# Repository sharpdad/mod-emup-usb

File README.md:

# MOD-EMUP over USB

Bring a 1990s universal device programmer back to life on a modern computer.

The **MOD-EMUP** (sold by JDR Microdevices; the same machine as the Hi-Lo
**ALL-03**, the Tribal TUP-400 and the Expro-60) programs parts that modern
programmers won't touch: bipolar PROMs (82S123, 82S129, 74S287, ...), old
PALs, GALs, PEELs and EPROMs. Arcade and vintage-computer people still need
those. But the box only talks to an 8-bit ISA card and DOS software.

This project replaces the ISA card with a small USB adapter and the DOS
software with a desktop app.

| | |
|---|---|
| **Status** | Designed, simulated and unit-tested. **Not yet tried on a real box.** |
| **Why it's posted** | The original author ran out of time. Everything needed to finish it is here; the missing piece is someone with a box, a meter and an afternoon. |

## What's here

| Folder | What | State |
|---|---|---|
| [`hardware/`](hardware/) | USB adapter PCB (KiCad 8): Arduino Nano, 74HCT245 / 74HCT244 bus buffers, DB25 to the box, and **one 12 V supply** for everything: +12 V passed through, +5 V 2 A from a RECOM R-78B switching module, -12 V from an isolated TRACO TMR 1-1211. All through-hole. Gerbers and BOM in `hardware/fab/`. Or build it on a breadboard with an old PC power supply: [`docs/BREADBOARD.md`](docs/BREADBOARD.md). | Routed, DRC clean. Not fabricated. |
| [`firmware/emup_usb/`](firmware/emup_usb/) | Arduino sketch: runs batches of register writes, reads and timed delays sent over USB serial (1 Mbaud), so programming pulses are timed on the adapter, not across USB. | Compiles in principle; untested. |
| [`app/`](app/) | **EMUP Studio**, a Tauri app (Rust + HTML) for macOS, Windows and Linux: chip search, a drawing of where the chip goes in the socket, drag-and-drop .bin / .hex / .jed, hex view, checksums, Read / Blank / Program / Verify. | Runs. 2716 read/program and 2732 read are implemented at register level against a model of the box; other chips use a placeholder. |
| [`dosbox-x/`](dosbox-x/) | A DOSBox-X patch that logs every port access the original DOS programs make, to learn each chip family's algorithm (voltages, pins, timings) without disassembling them. | Works; findings in its README. |
| [`docs/`](docs/) | [Register map and cable pinout](docs/NOTES.md), notes. | |
| [`tools/kicad/`](tools/kicad/) | The scripts that generate the KiCad schematic and routed PCB from `hardware/emup_adapter.py`. | Works. |

## How the box works

The ISA card is just a buffered bus extender: an 8-bit data bus and three
strobes go down a DB25 cable. Everything else is in the box. Software
writes a register number to the card's **ID port**, then reads or writes
that register through the **data port**:

| Register | Does |
|---|---|
| E0-E4 | TTL I/O for socket pins 1-40 (open collector: write 1 before reading or applying a supply) |
| E5 / E6 / E7 | VOP (0.1 V steps) / VHH (0.06 V) / VCC (0.04 V) DACs |
| E8-EC, F0-F4 | switch VOP / VHH onto socket pins |
| ED-EE | switch VCC onto a fixed set of pins |
| EF | ground selection (pin 20 or pins 11 / 30), clocks |
| F7 | bit 3: GOOD lamp |

Full map and the DB25 pinout: [docs/NOTES.md](docs/NOTES.md). Chips sit at
the bottom of the 40-pin socket; chip pin *k* lands on socket pin
*k* + 20 - pins/2, so a 2716's ground lands on socket pin 20 and its VCC on
pin 32, both of which the box can switch.

## Building the adapter

1. Order the board from `hardware/fab/emup_adapter_gerbers.zip` (any 2-layer
   fab) and the parts in `hardware/fab/bom.csv`.
2. **Before plugging into a box:** check the DB25 pinout in
   [docs/NOTES.md](docs/NOTES.md) against your box with a meter. It comes from
   Tom Trebisky's notes on his card; boxes and cables may differ.
3. Power the board alone from a 12 V, 2 A supply (2.1 mm, centre positive)
   and check +5 V, +12 V and -12 V on the DB25 pins.
4. Flash `firmware/emup_usb/emup_usb.ino` to the Nano (Arduino IDE).
5. Connect the box, run the app, pick the adapter's serial port.

The box's real current draw is unknown. The +5 V module gives 2 A and the
-12 V module about 80 mA; measure the box and change the modules if needed.

## Building the app

```sh
cd app/src-tauri
cargo install tauri-cli --version "^2"
cargo tauri dev        # run
cargo tauri build      # make an installable app
cargo test             # the box model: read and program a virtual 2716
```

Needs Rust ([rustup.rs](https://rustup.rs)). Windows also needs WebView2,
which Windows 10 and 11 include.

## What's left to do (good first issues)

* **Try it on a real box.** Measure current draw, confirm the pinout, read a
  known 2716 and compare it with a dump made elsewhere.
* **The identification check.** Every DOS program first checks the box: it
  writes 00, 01, 00, 02 and then pulses to register E7 and reads the low
  nibble of register **F8**, which the ALL-03 documentation doesn't mention.
  The app doesn't need it, but it shows there's logic in the box we don't
  fully understand. See [dosbox-x/README.md](dosbox-x/README.md).
* **More chip algorithms** in `app/src-tauri/src/emup.rs`: 2732 / 27xx
  programming, bipolar PROMs (fuse blowing: VOP pulses on the outputs),
  PAL/GAL programming from JEDEC fuse maps. Record the DOS programs with the
  DOSBox-X patch to see exactly what they do.
* **Release builds** of EMUP Studio for macOS / Windows / Linux (GitHub
  Actions can build all three).

## Credits and sources

* Tom Trebisky's pages on the MOD-EMUP and ALL-03 (cable, card, protocol):
  http://cholla.mmto.org/proms/emup/
* The ALL-03 register description (`all03info.txt`, by the manufacturer,
  with a note by Fabio Sturman) and the ALL-03 manual, findable in vintage
  programmer archives.

The original DOS software, sample images and third-party documents are not
included; find them through the links above.

## Licence

Code (app, firmware, tools, patch): MIT, see [LICENSE](LICENSE); the DOSBox-X
patch is GPL-2.0 like DOSBox-X. Hardware design: CERN-OHL-P-2.0.

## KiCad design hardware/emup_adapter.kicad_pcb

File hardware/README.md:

# The USB adapter PCB

`emup_adapter.py` describes the board (parts, nets, placement);
`./build.sh` turns it into the KiCad schematic (`emup_adapter.kicad_sch`,
`.pdf`), a routed PCB (`emup_adapter.kicad_pcb`), DRC / ERC reports and fab
files (`fab/`: Gerber + drill zip, BOM). The KiCad files open and edit
normally in KiCad 8; if you edit the board by hand, don't re-run build.sh.

* Power: one 12 V DC supply (2.1 mm barrel, centre positive, 2 A) through
  a 1N5822. +12 V goes to the box as is; +5 V (2 A) comes from a RECOM
  R-78B5.0-2.0 (7805-footprint switching module); -12 V from a TRACO TMR
  1-1211 isolated module with its +output tied to ground (about 80 mA). The
  power nets are 1 mm tracks (`netclasses.json`).
* Logic: an Arduino Nano (5 V, on USB) drives D0-D7 through a 74HCT245
  (direction from D10) and the strobes /WRID, /WRDAT, /RDDAT and /RESET
  through a 74HCT244 (from A0-A3). 10k pull-ups hold the strobes idle while
  the Nano boots. The buffers run from the board's +5 V.
* DB25 female, wired as the original SAC-201 card (pinout in
  ../docs/NOTES.md). Check it against your box first.

Untested. Things to check on the first board: the box's current on each
rail, the -12 V module's load, the DB25 pinout, and the strobe timing (the
firmware uses ~1 us strobes, like the ISA bus).

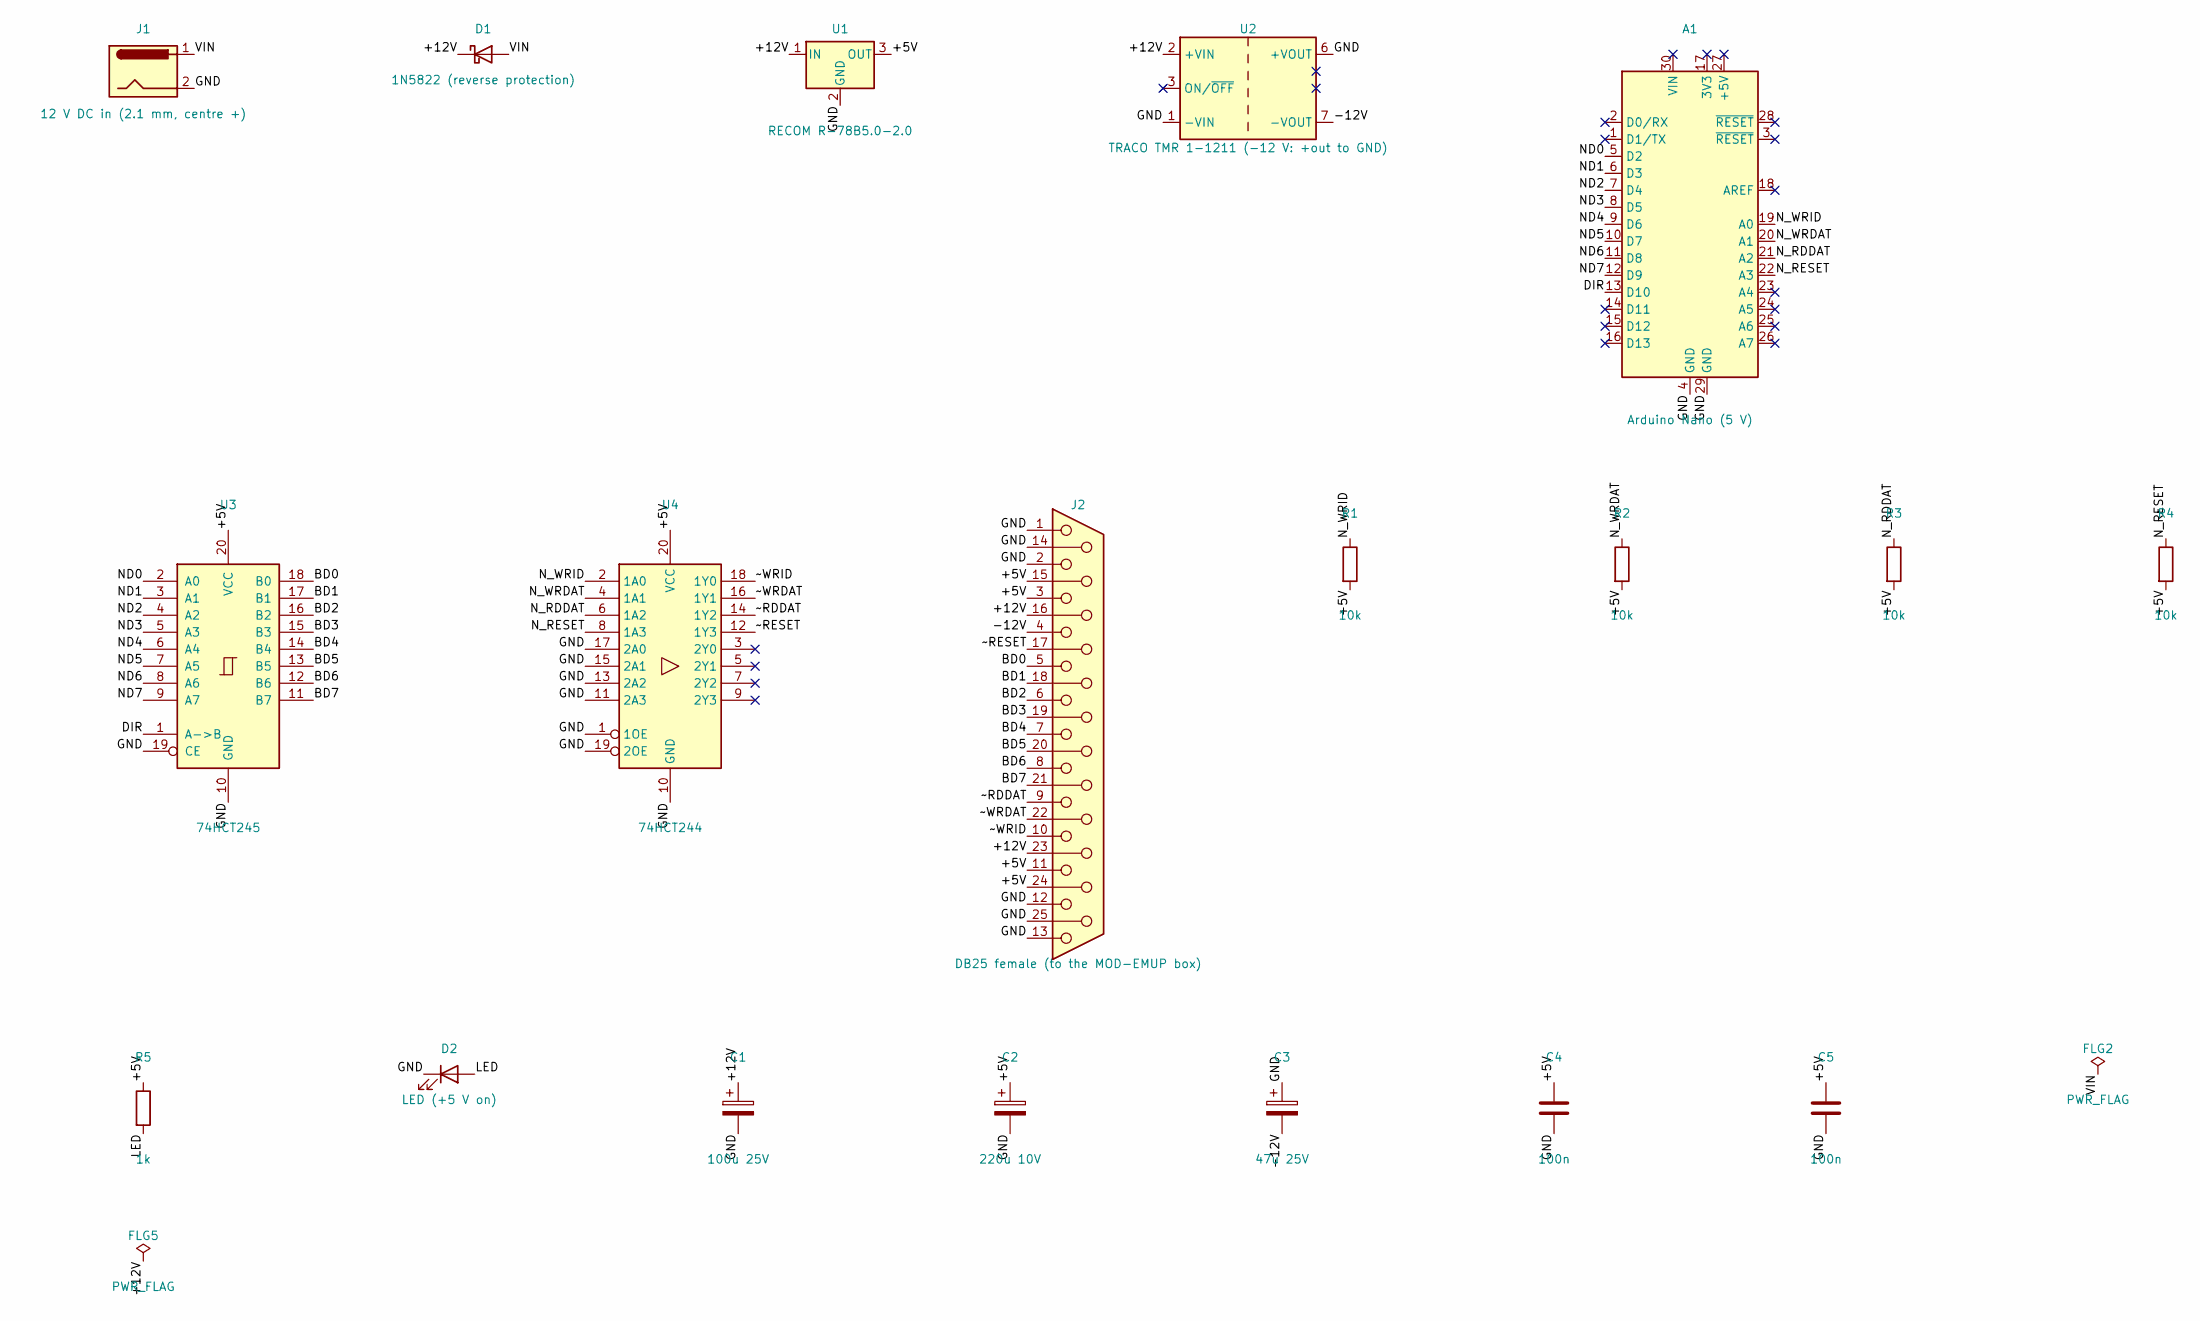
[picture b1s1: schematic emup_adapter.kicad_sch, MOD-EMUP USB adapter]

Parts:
A1: Arduino Nano (5 V); Arduino_Nano
C1: 100u 25V; CP_Radial_D8.0mm_P3.50mm
C2: 220u 10V; CP_Radial_D8.0mm_P3.50mm
C3: 47u 25V; CP_Radial_D6.3mm_P2.50mm
C4, C5: 100n; C_Disc_D5.0mm_W2.5mm_P5.00mm
D1: 1N5822 (reverse protection); D_DO-201AD_P15.24mm_Horizontal
D2: LED (+5 V on); LED_D3.0mm
FLG2, FLG5: PWR_FLAG
J1: 12 V DC in (2.1 mm, centre +); BarrelJack_Horizontal
J2: DB25 female (to the MOD-EMUP box); DSUB-25_Female_Horizontal_P2.77x2.84mm_EdgePinOffset14.56mm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
R1, R2, R3, R4: 10k; R_Axial_DIN0207_L6.3mm_D2.5mm_P10.16mm_Horizontal
R5: 1k; R_Axial_DIN0207_L6.3mm_D2.5mm_P10.16mm_Horizontal
U1: RECOM R-78B5.0-2.0; Converter_DCDC_RECOM_R-78B-2.0_THT
U2: TRACO TMR 1-1211 (-12 V: +out to GND); Converter_DCDC_TRACO_TMR-1-xxxx_Single_THT
U3: 74HCT245; DIP-20_W7.62mm_Socket
U4: 74HCT244; DIP-20_W7.62mm_Socket

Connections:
+5V: C2.1, C4.1, C5.1, J2.3, J2.11, J2.15, J2.24, R1.2, R2.2, R3.2, R4.2, R5.1, U1.3 (OUT), U3.20 (VCC), U4.20 (VCC)
+12V: C1.1, D1.1 (K), FLG5.1, J2.16, J2.23, U1.1 (IN), U2.2 (+VIN)
-12V: C3.2, J2.4, U2.7 (-VOUT)
BD0: J2.5, U3.18 (B0)
BD1: J2.18, U3.17 (B1)
BD2: J2.6, U3.16 (B2)
BD3: J2.19, U3.15 (B3)
BD4: J2.7, U3.14 (B4)
BD5: J2.20, U3.13 (B5)
BD6: J2.8, U3.12 (B6)
BD7: J2.21, U3.11 (B7)
DIR: A1.13 (D10), U3.1 (A->B)
GND: A1.4 (GND), A1.29 (GND), C1.2, C2.2, C3.1, C4.2, C5.2, D2.1 (K), J1.2, J2.1, J2.2, J2.12, J2.13, J2.14, J2.25, U1.2 (GND), U2.1 (-VIN), U2.6 (+VOUT), U3.10 (GND), U3.19 (CE), U4.1 (1OE), U4.10 (GND), U4.11 (2A3), U4.13 (2A2), U4.15 (2A1), U4.17 (2A0), U4.19 (2OE)
LED: D2.2 (A), R5.2
ND0: A1.5 (D2), U3.2 (A0)
ND1: A1.6 (D3), U3.3 (A1)
ND2: A1.7 (D4), U3.4 (A2)
ND3: A1.8 (D5), U3.5 (A3)
ND4: A1.9 (D6), U3.6 (A4)
ND5: A1.10 (D7), U3.7 (A5)
ND6: A1.11 (D8), U3.8 (A6)
ND7: A1.12 (D9), U3.9 (A7)
N_RDDAT: A1.21 (A2), R3.1, U4.6 (1A2)
N_RESET: A1.22 (A3), R4.1, U4.8 (1A3)
N_WRDAT: A1.20 (A1), R2.1, U4.4 (1A1)
N_WRID: A1.19 (A0), R1.1, U4.2 (1A0)
VIN: D1.2 (A), FLG2.1, J1.1
~RDDAT: J2.9, U4.14 (1Y2)
~RESET: J2.17, U4.12 (1Y3)
~WRDAT: J2.22, U4.16 (1Y1)
~WRID: J2.10, U4.18 (1Y0)

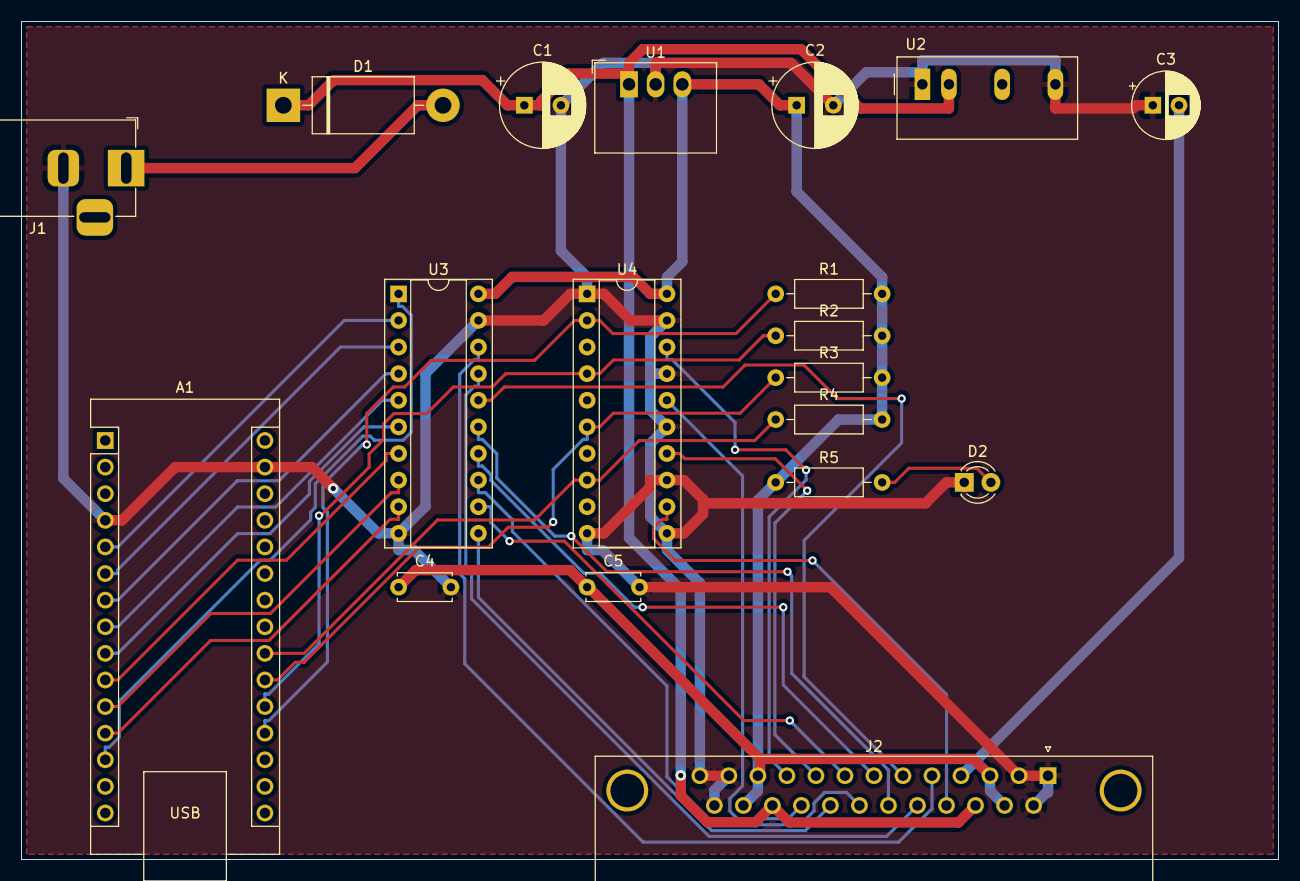
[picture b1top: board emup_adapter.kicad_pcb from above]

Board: 2 copper layers, 120.0 x 80.0 mm, 19 parts (0 on the bottom side), 31 nets.

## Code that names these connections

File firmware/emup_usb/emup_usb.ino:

// MOD-EMUP USB adapter: an Arduino (5 V) in place of the SAC-201 ISA card.
//
// The box needs only what the ISA card gave it: an 8-bit data bus, three
// active-low strobes (write ID port, write data port, read data port) and
// /RESET, plus power (+5 V, +12 V, -12 V from a separate supply, NOT from
// the Arduino). See emup/README.md for the DB25 pinout. Put a 74LS245 on
// the data bus and a 74LS244 on the strobes, as the card had.
//
// Host protocol (USB serial, 1,000,000 baud): a batch is
//   'B' len_lo len_hi  <len bytes of ops>
// ops:
//   0x01 id         write the ID port
//   0x02 v          write the data port
//   0x03            read the data port (one byte back)
//   0x04 id v       ID then data (the usual register write)
//   0x05 id         ID then read (one byte back)
//   0x06 lo hi      wait lo + 256 hi microseconds
//   0x07 lo hi      wait lo + 256 hi milliseconds
//   0x08            pulse /RESET (the box clears every register)
// The adapter runs the whole batch, so programming pulses are timed here,
// not across USB, then replies 'K' + the bytes read, in order. 'V' replies
// "EMUP1\n". Batches are capped at 4 KB.
//
// Pins (Arduino Nano / Uno; change to suit):
//   D2-D9   data bus D0-D7 (through the 74LS245)
//   D10     245 direction (high: Arduino -> box)
//   A0      /WRID   (write ID port, DB25 pin 10)
//   A1      /WRDAT  (write data port, DB25 pin 22)
//   A2      /RDDAT  (read data port, DB25 pin 9)
//   A3      /RESET  (DB25 pin 17)

const uint8_t DATA_PINS[8] = {2, 3, 4, 5, 6, 7, 8, 9};
const uint8_t DIR = 10;
const uint8_t WRID = A0, WRDAT = A1, RDDAT = A2, RST = A3;

static uint8_t batch[4096];

static void busOut(uint8_t v) {
  digitalWrite(DIR, HIGH);
  for (uint8_t i = 0; i < 8; i++) {
    pinMode(DATA_PINS[i], OUTPUT);
    digitalWrite(DATA_PINS[i], (v >> i) & 1);
  }
}

static uint8_t busIn() {
  for (uint8_t i = 0; i < 8; i++) pinMode(DATA_PINS[i], INPUT);
  digitalWrite(DIR, LOW);
  return 0;
}

static void strobe(uint8_t pin) {
  digitalWrite(pin, LOW);
  delayMicroseconds(1);           // the ISA cycle was ~1 us
  digitalWrite(pin, HIGH);
}

static void writeId(uint8_t id) { busOut(id); strobe(WRID); }
static void writeData(uint8_t v) { busOut(v); strobe(WRDAT); }

static uint8_t readData() {
  busIn();
  digitalWrite(RDDAT, LOW);
  delayMicroseconds(1);
  uint8_t v = 0;
  for (uint8_t i = 0; i < 8; i++) v |= digitalRead(DATA_PINS[i]) << i;
  digitalWrite(RDDAT, HIGH);
  return v;
}

static int readByte() {
  while (!Serial.available()) {}
  return Serial.read();
}

void setup() {
  for (uint8_t p : {WRID, WRDAT, RDDAT, RST}) { pinMode(p, OUTPUT); digitalWrite(p, HIGH); }
  pinMode(DIR, OUTPUT);
  busIn();
  Serial.begin(1000000);
}

void loop() {
  int c = readByte();
  if (c == 'V') { Serial.print("EMUP1\n"); return; }
  if (c != 'B') return;
  uint16_t len = readByte();
  len |= (uint16_t)readByte() << 8;
  if (len > sizeof batch) len = sizeof batch;
  for (uint16_t i = 0; i < len; i++) batch[i] = readByte();
  Serial.write('K');
  for (uint16_t i = 0; i < len;) {
    switch (batch[i++]) {
      case 0x01: writeId(batch[i++]); break;
      case 0x02: writeData(batch[i++]); break;
      case 0x03: Serial.write(readData()); break;
      case 0x04: writeId(batch[i]); writeData(batch[i + 1]); i += 2; break;
      case 0x05: writeId(batch[i++]); Serial.write(readData()); break;
      case 0x06: { uint16_t us = batch[i] | (batch[i + 1] << 8); i += 2;
                   while (us > 16000) { delayMicroseconds(16000); us -= 16000; }
                   delayMicroseconds(us); break; }
      case 0x07: { uint16_t ms = batch[i] | (batch[i + 1] << 8); i += 2; delay(ms); break; }
      case 0x08: digitalWrite(RST, LOW); delay(1); digitalWrite(RST, HIGH); delay(1); break;
      default: i = len; break;    // unknown op: stop
    }
  }
}
